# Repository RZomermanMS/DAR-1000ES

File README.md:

# Sony DAR-1000ES Conversion Project

This repository contains the project documentation converted from the original Word document into chapter-based GitHub Flavored Markdown.

## Chapters

For current AHCT wiring, brightness calculations and radio operation, start
with the [screen-driver operating guide](13-screen-driver-operating-guide.md).
Shared STB on **both** TD chips corrected the earlier multiplexing corruption;
clean 22-matrix text and scrolling were observed. Firmware 0.3.28 includes
internet radio, explicitly authorized full-width NOW PLAYING, and source
channel/bitrate/playback/genre indicators.
Installed 0.3.29 adds selectable Option 1 stereo spectrum (11 real PCM frequency
bands per channel), verified with isolated TD-model captures and decoded
stereo/mono/silence fixtures; the user confirmed the bars at 0.75% brightness.
Version 0.3.30 adds MONO 1/2 bank labels while retaining actual-source STEREO
and fixes measured scan gaps with longer DMA batching. A connected camera
snapshot confirms all 22 bars and STEREO/MONO 1/MONO 2/TUNED at 0.75%
per-grid duty. User confirmation of residual flicker is still pending;
a still image cannot establish temporal stability.
Physical voltage/current validation remains outstanding.
Firmware 0.3.31 boots with the fixed AHCT v2 GPIO map. Display output still
starts stopped; the legacy profile remains an isolated-only runtime option.
Installed firmware 0.3.32 adds eight display modes and shared short-/long-press
controls for a future Display Mode button, with 0.25% / 0.5% / 0.75% DIM cycling.
All eight modes and DIM cycling were checked on the isolated ESP; after
reconnection, Equalizer was restored at 0.75% per-grid duty.

For current display control, start with the
[fixed-element guide](08-esp-display-driver-specification.md#6-fixed-element-control-guide)
and [generic 5x7 matrix guide](08-esp-display-driver-specification.md#7-generic-5x7-matrix-guide).
The [annotated reference comparison](media/display-reference-coverage.svg)
matches every functional symbol in the FL701 drawing to an observed command.
Element mapping is complete at that level. Clean full-screen multiplexing
has now been observed with shared STB; electrical validation remains outstanding.

The [complete display bitmap catalogue](10-display-bitmap-catalogue.md)
includes 5x7 pixel patterns and HEX values for uppercase/lowercase letters,
digits, punctuation, a music note and seven level bars.

1. [DAR-1000ES Conversion](01-conversion.md)
2. [DAR-1000ES Display Control](02-display-control.md)
3. [DAR-1000ES Sound Path](03-sound-path.md)
4. [DAR-1000ES Program and Keypad Baseline](04-program-and-keypad-baseline.md)
5. [Bus Capture Findings and Key Reports](05-bus-capture-findings.md)
6. [Direct Display driving](06-direct-display-driving.md)
7. [Audio Control Findings and Next-Step Plan](07-audio-control-findings-and-plan.md)
8. [ESP32 Display-Driver Specification](08-esp-display-driver-specification.md)
9. [Music Note Bitmap](09-music-note-bitmap.md)
10. [Display Bitmap Catalogue](10-display-bitmap-catalogue.md)
11. [Live ESP32 Display Driver and Validation](11-live-display-driver-and-validation.md)
12. [TD62C950RF Timing Revalidation](12-td62c950rf-timing-revalidation.md)
13. [Screen Driver Operating Guide](13-screen-driver-operating-guide.md)
14. [Keypad Mapping](14-keypad-mapping.md)
15. [Split-setup Architecture and Travel Demo](15-split-setup-architecture.md)
16. [Internet-radio Menu Program Guide (proposed)](16-internet-radio-menu-program-guide.md)
17. [Internet-radio Menu User Instruction Manual (planned)](17-internet-radio-menu-user-manual.md)
18. [Controller ESP Implementation Specification and Agent Handoff](18-controller-esp-implementation-specification.md)

Chapters 16–17 describe a proposed directory/menu design, **not installed
firmware behavior**. For implemented controls and safety requirements, continue
to use chapters 13–15.

Images used by the chapters are stored in [`media/`](media/).

The [ESP32 firmware](firmware/README-DAR-1000ES.md) includes internet radio,
the opt-in display timing/NOW PLAYING profile and the preserved upstream license.

## Control Integration Options

1. **Reuse the original controls (partially characterized):** Investigate the parallel bus between the system controller and display/front-panel controller IC701 before bypassing the original control firmware. See the [internal bus protocol specification](SONY_DAR1000ES_Protocol_Spec.md) and [2026-11-02 capture findings](05-bus-capture-findings.md). Passive captures establish repeatable framing and key/display correlations, but masked bits, driver ownership and electrical assumptions still block reliable emulation.
2. **Direct display-driver control (optically mapped, driver experimental):** Captures at IC702/IC703 establish a 26-slot scan, 40 segment clocks and one grid clock per slot. Controlled one-hot tests now map all 770 matrix dots and all fixed functional elements shown in the reference. See the [operating guide](13-screen-driver-operating-guide.md), [element guide](08-esp-display-driver-specification.md) and [capture/validation history](06-direct-display-driving.md). Shared STB on both TD chips now gives clean full-width text and scrolling; electrical margins and current remain unverified. [DAR-1000ES Display Control](02-display-control.md) retains the original hardware proposal, not current wiring instructions.

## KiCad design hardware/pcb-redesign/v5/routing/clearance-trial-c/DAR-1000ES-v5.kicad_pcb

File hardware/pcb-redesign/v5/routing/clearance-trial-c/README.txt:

Trial C — local clearance experiment, NOT fabrication-ready
==========================================================

This is an independent derivative of placement-trial B, not an integration
with any other trial. It keeps B's placement, board outline, two antenna rule
areas, vias, pad and footprint geometry, widths, nets and all other board
data. Only endpoints of five existing B.Cu segments move at three junctions.
No new rules, exclusions, pads, layers or router were used. The long U5-VIN
segment is now slightly slanted; adjacent segments are no longer necessarily
45 degrees. Inspect manufacturability and assembly separately.

Source board SHA-256:
  2a6f2adb1d2c4078de47b7a6d337af844bace43cf1a1155d9afe8d2e7d51e7e8
Candidate board SHA-256:
  f99f7348a54bc94fd867fb7ec5e5e0f9a544eb5cf260c7a8530197dcbbef90fb
Project SHA-256:
  50232cc98a9d9072bd8f43c5f5ec578d815ad27146f54a17ccc97d2d18c3a5ed
The schematic copies are byte-identical to the original v5 hierarchy and
are retained beside the same-stem board and project for parity checks. The
footprint table points back to the original v5 library.

Observed changes, native KiCad copper-shape distances
---------------------------------------------------
Measurements compare the retained placement-trial/trial-b-tht-clearance.json
with tht-clearance.json, using the same KiCad 10.0.2 tool and 0.50 mm cutoff.
Unrelated plated-through-hole pad vs track/via pairs are counted per common
copper layer and segment, not unique locations.

* U11 pad 3 to the horizontal SONY_5V_SENSE segment, B.Cu:
  0.201700 -> 0.351701 mm; this is also that pad's measured local minimum.
* U1-CONTROLLER1 J3.11–J3.22 to the long U5-VIN segment, B.Cu: each
  0.201700 -> 0.398570 down to 0.224405 mm, respectively.
  At J3.11 the adjacent diagonal improves 0.201657 -> 0.261535 mm;
  that diagonal remains the pad's nearest unrelated track.
* Across the entire board, pairs below 0.30 mm decrease from 330 to 322;
  the 0.50 mm report has 465 pairs both before and after. Among pairs present
  in both reports 14 distances increase and none decrease; no pairs enter or
  leave that cutoff. This comparison does not imply anything about pairs
  outside the cutoff, pad-to-pad, zones, non-PTH holes or non-PTH pads.
* The board-wide minimum remains 0.201657 mm at another pad/track pair.
  Thus this does NOT establish generous or universal 0.30 mm spacing.

The initial test moved the entire U5-VIN segment 0.20 mm left and the IO4
segment by R3 0.15 mm upward, along with the U11 move. It failed native DRC:
four track-to-track conflicts at IO4/IO42 and a 0.1828 mm track-to-C8 pad
gap. Those shifts were not retained. The final change moves only the upper
U5-VIN junction, preserving its remote diagonal and avoiding that conflict.
No claim is made that this small, local search is optimal or exhaustive.

Validation and limitations
--------------------------
drc.json and drc-parity.json: native KiCad 10.0.2, zero violations, zero
unconnected items; the latter also reports zero schematic parity issues.
The project has no DRC exclusions and missing-courtyard is an error. Four
checks remain ignored: track_not_centered_on_via, tuning_profile_track_
geometries, footprint_filters_mismatch, footprint_type_mismatch. A zero
report does not verify them. audit.txt records the retained netlist/319 node,
exact UART endpoints, y=150 mm section and component-envelope audits.
It also verifies the exact board text differs only in the five intended
segment endpoint coordinates; there are 715 segments, seven vias and 0.30 mm
minimum track width. The retained measurement and board-audit unit suites
passed (7 and 10 tests). These audits do not model plugs, cables, installed
modules, chassis, RF, electrical return paths or the actual antenna keepout.
Trial B's decoupling limitations still apply; no circuit, mechanical, thermal,
RF, safety, fabrication or assembly approval is implied.

Reproduction (repository root)
------------------------------
Requires Docker image kicad/kicad:10.0.2 (observed digest
sha256:165c81785b2df23a09892f4cc53bc0095a83b469bfbbe07989670d64049677a7).
Use an existing writable OUT directory outside the repository. No router JAR
is needed. The container runs with the repository read-only; HOME is
deliberately unwritable, so KiCad may print configuration-directory errors.

  P=hardware/pcb-redesign/v5/routing/clearance-trial-c
  V=hardware/pcb-redesign/v5
  docker run --rm --network none --user "$(id -u):$(id -g)" \
    -e HOME=/nonexistent -e PYTHONDONTWRITEBYTECODE=1 \
    -v "$PWD:/work:ro" -v "$OUT:/out:rw" --entrypoint /usr/bin/python3 \
    kicad/kicad:10.0.2 /work/$P/build.py \
    /work/$V/routing/placement-trial/silk-b/result.kicad_pcb /out/rebuilt.kicad_pcb
  sha256sum "$OUT/rebuilt.kicad_pcb" "$P/DAR-1000ES-v5.kicad_pcb"
  docker run --rm --network none --user "$(id -u):$(id -g)" \
    -e HOME=/nonexistent -e PYTHONDONTWRITEBYTECODE=1 -v "$PWD:/work:ro" \
    -v "$OUT:/out:ro" --entrypoint /usr/bin/python3 kicad/kicad:10.0.2 \
    /work/$P/audit.py /work/$V/routing/placement-trial/silk-b/result.kicad_pcb \
    /out/rebuilt.kicad_pcb /work/$V/DAR-1000ES-v5.net.xml
  docker run --rm --network none --user "$(id -u):$(id -g)" \
    -e HOME=/nonexistent -v "$PWD:/work:ro" --entrypoint kicad-cli \
    kicad/kicad:10.0.2 pcb drc --schematic-parity --format json -o /dev/stdout \
    /work/$P/DAR-1000ES-v5.kicad_pcb
  docker run --rm --network none --user "$(id -u):$(id -g)" \
    -e HOME=/nonexistent -e PYTHONDONTWRITEBYTECODE=1 -v "$PWD:/work:ro" \
    --entrypoint /usr/bin/python3 kicad/kicad:10.0.2 \
    /work/$V/routing/measure_tht_clearance.py /work/$P/DAR-1000ES-v5.kicad_pcb

The parity command checks the retained candidate; first compare the rebuilt
hash to establish it is the same board. Separate normal DRC omits
--schematic-parity. Report dates and tool logs need not be bit-identical.

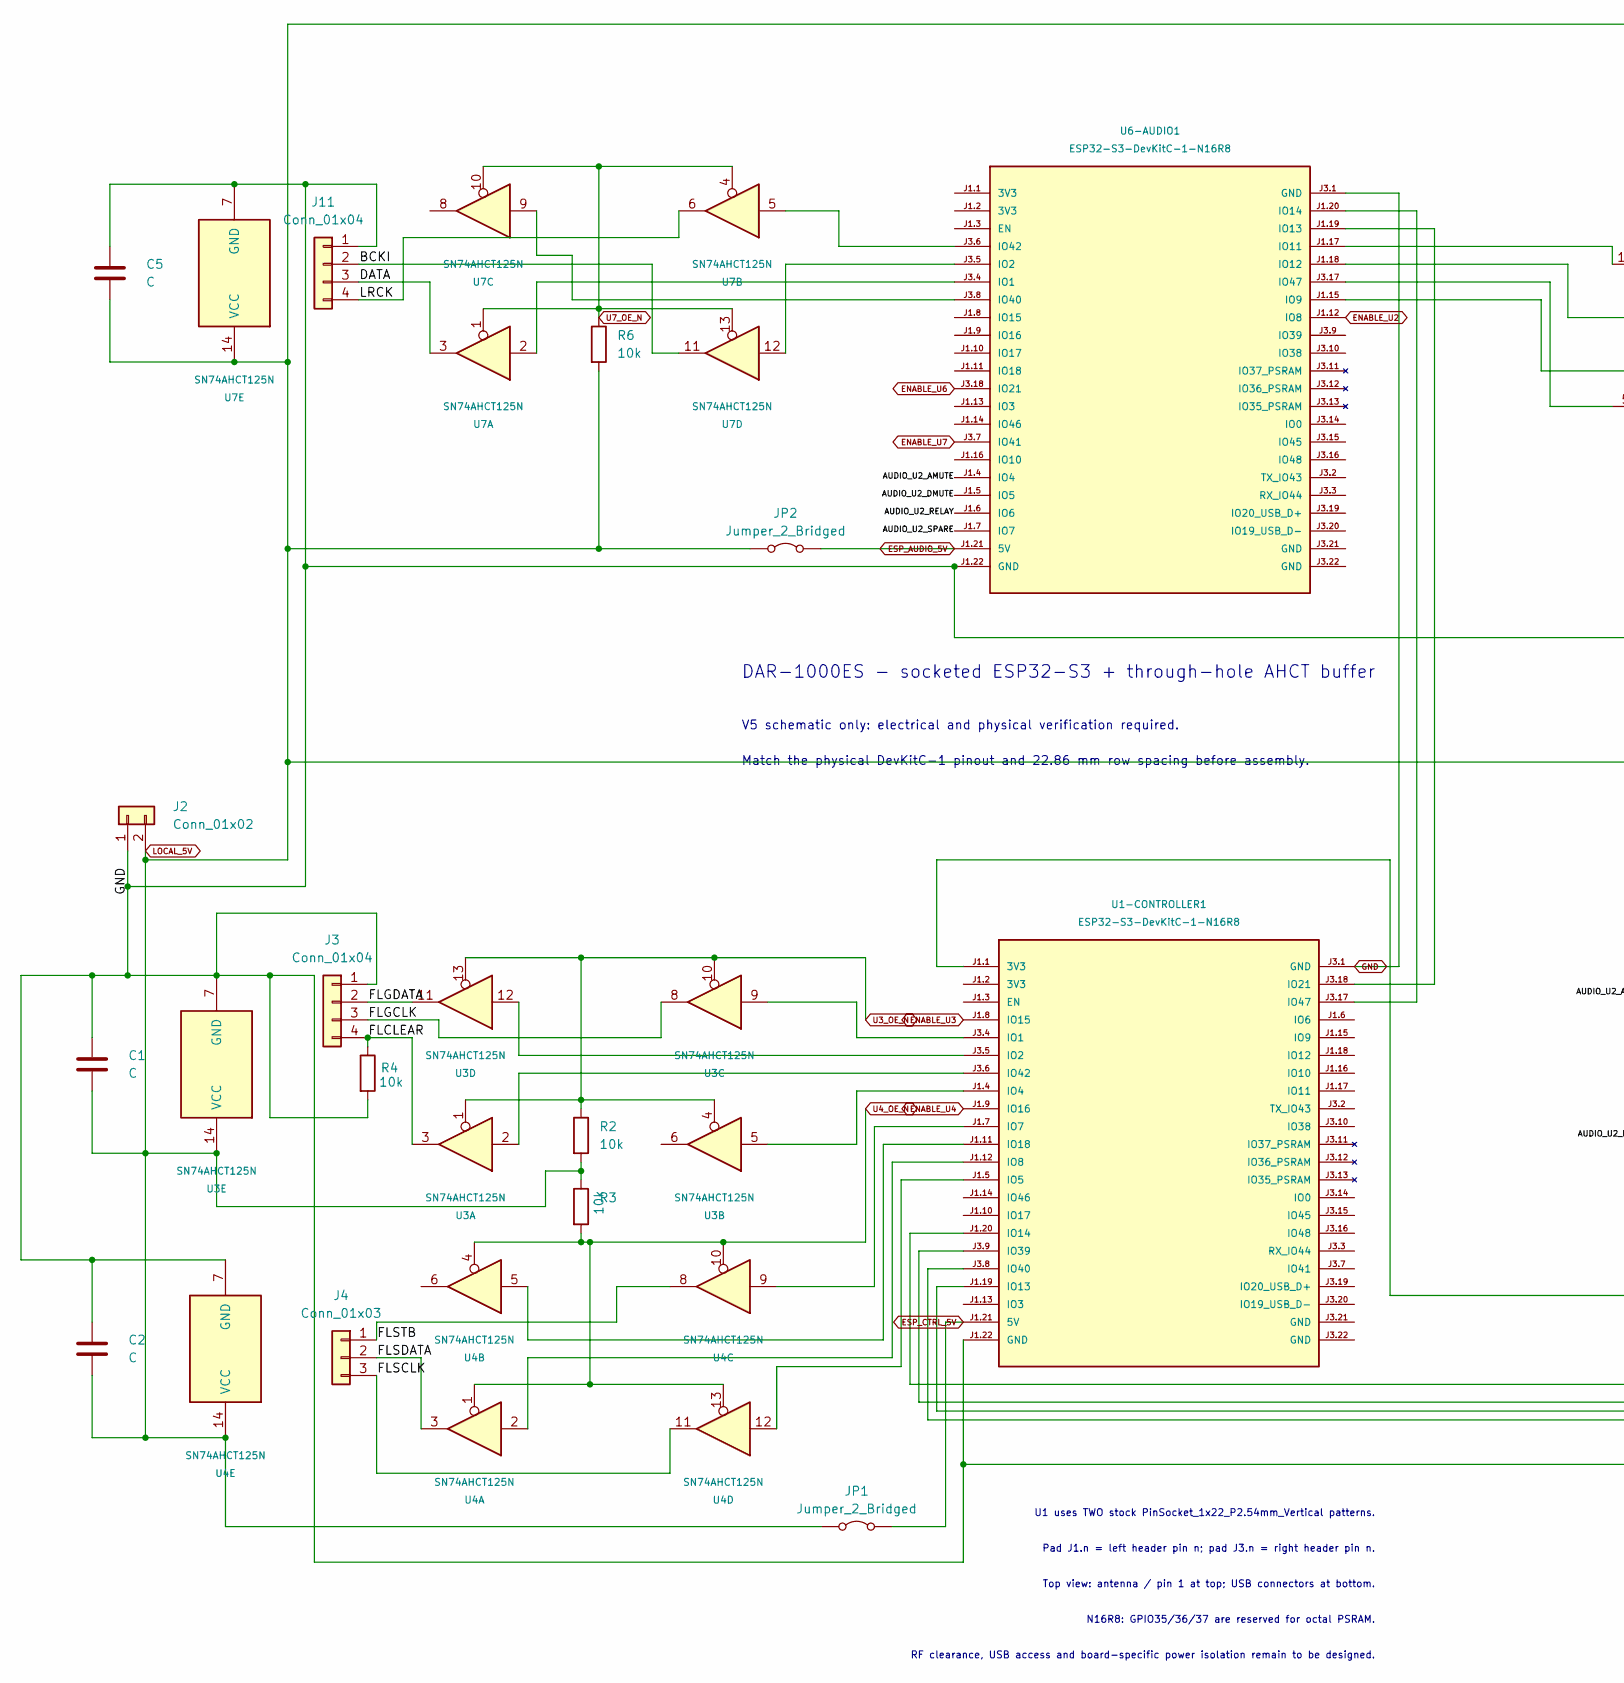
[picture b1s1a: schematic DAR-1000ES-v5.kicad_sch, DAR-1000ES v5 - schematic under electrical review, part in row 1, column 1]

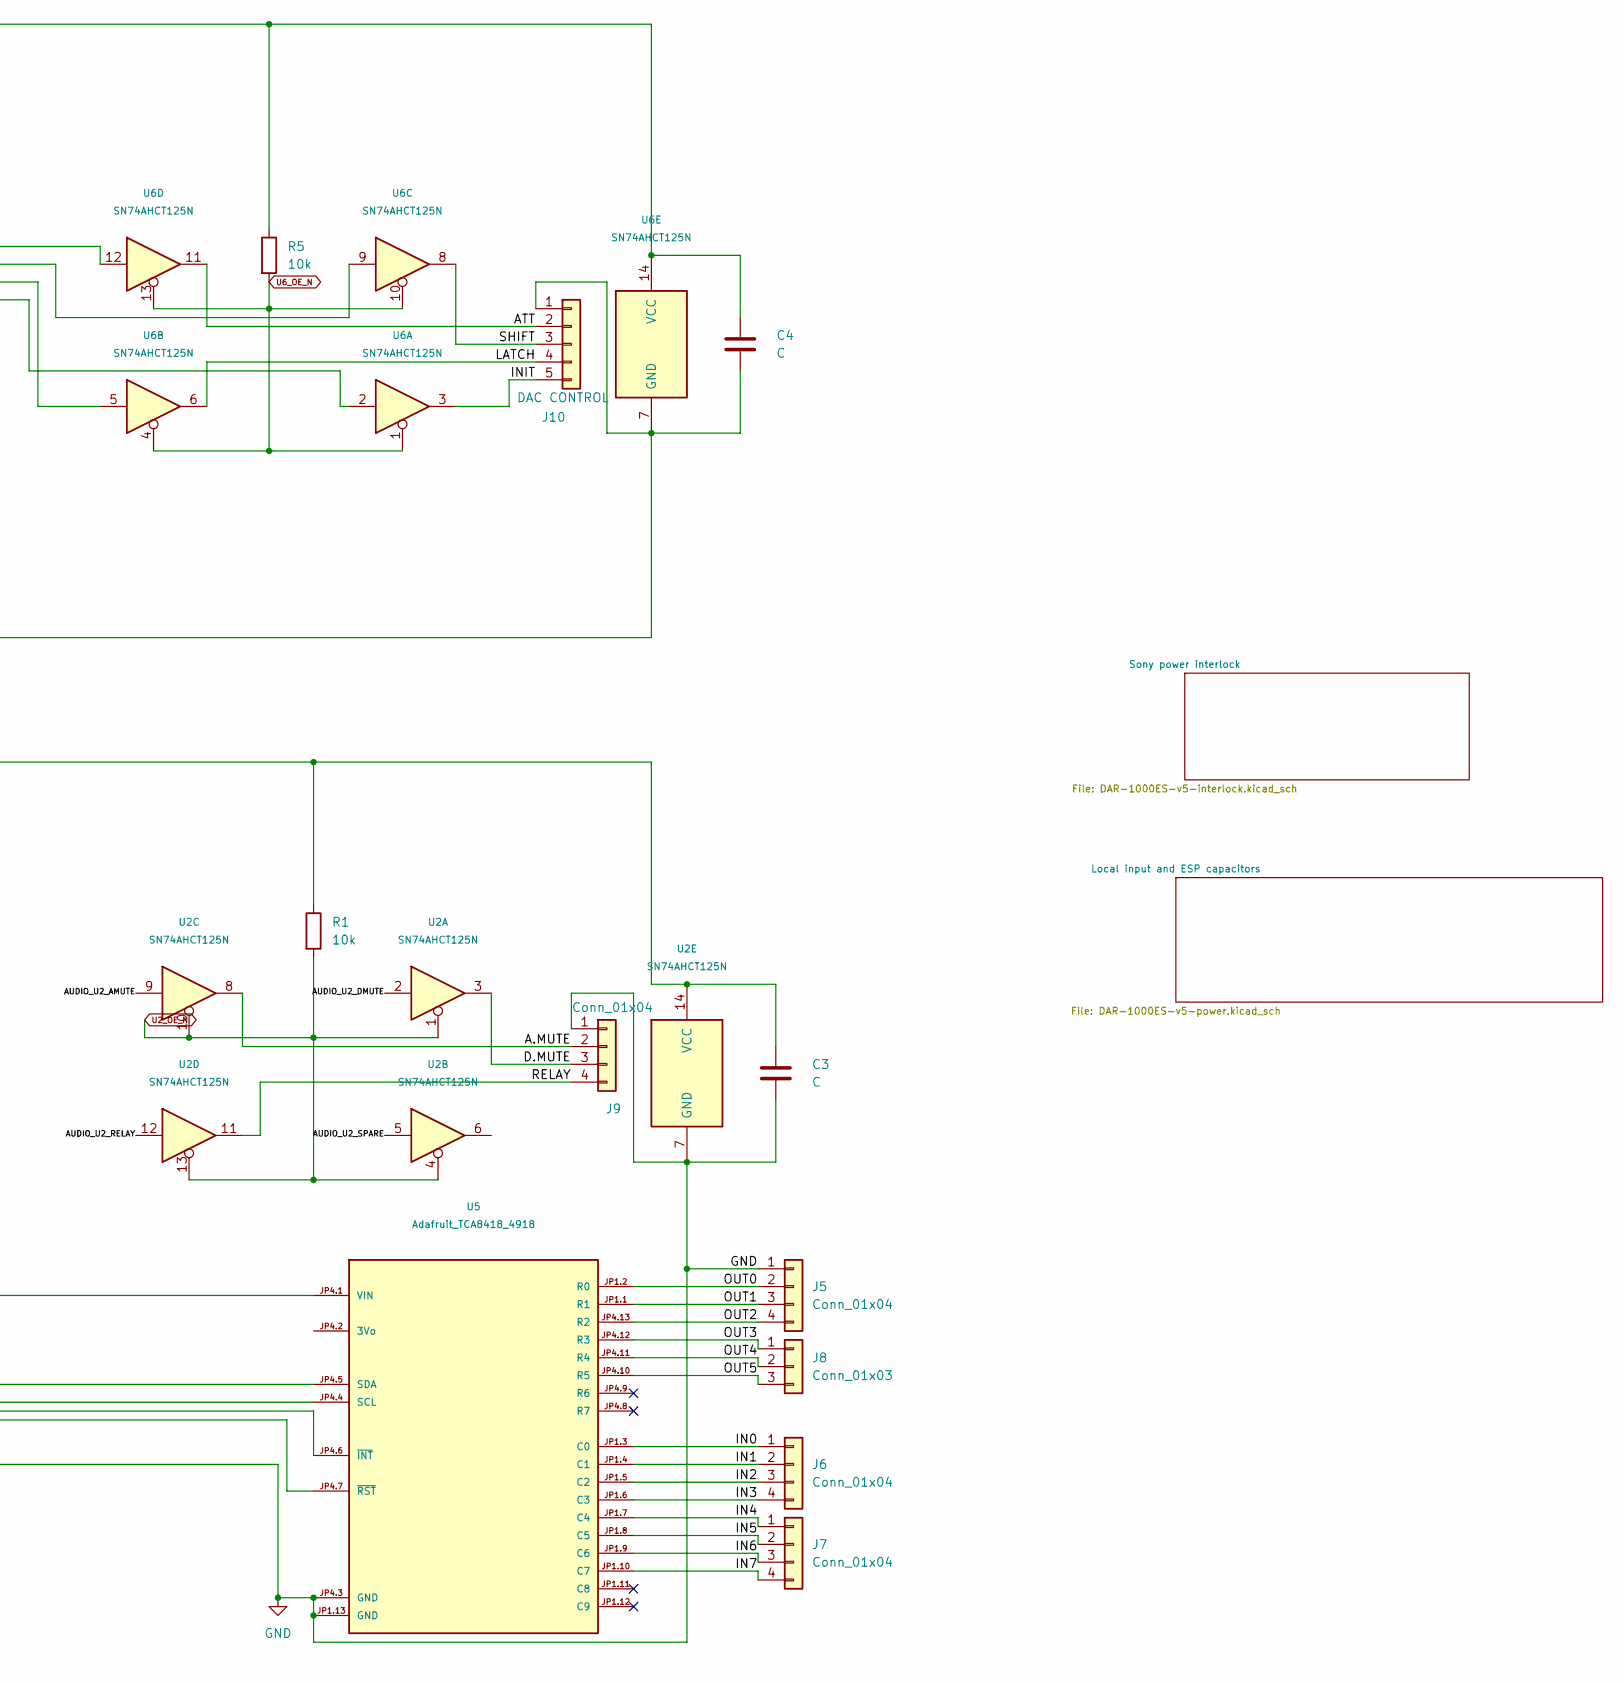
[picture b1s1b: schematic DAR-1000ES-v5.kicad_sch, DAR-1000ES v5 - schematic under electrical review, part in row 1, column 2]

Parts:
C1, C2, C3, C4, C5: C; Bottom_Capacitor_THT__C_Disc_D5.0mm_W2.5mm_P5.00mm
J2: Conn_01x02; Bottom_Connector_JST__JST_XH_S2B-XH-A_1x02_P2.50mm_Horizont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
J3, J5, J6, J7, J9, J11: Conn_01x04; Bottom_Connector_JST__JST_XH_S4B-XH-A_1x04_P2.50mm_Horizont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
J4, J8: Conn_01x03; Bottom_Connector_JST__JST_XH_S3B-XH-A_1x03_P2.50mm_Horizont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
J10: DAC CONTROL; Bottom_Connector_JST__JST_XH_S5B-XH-A_1x05_P2.50mm_Horizont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
JP1, JP2: Jumper_2_Bridged; Bottom_Connector_PinHeader_2.54mm__PinHeader_1x02_P2.54mm_V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
R1, R2, R3, R4, R5, R6: 10k; Bottom_Resistor_THT__R_Axial_DIN0207_L6.3mm_D2.5mm_P7.62mm_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
U1-CONTROLLER1, U6-AUDIO1: ESP32-S3-DevKitC-1-N16R8; Bottom_DAR1000ES__ESP32-S3-DevKitC-1_2xSocket_1x22_P2.54mm_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; MPN ESP32-S3-DevKitC-1-N16R8
U2, U3, U4, U6, U7: SN74AHCT125N; Bottom_Package_DIP__DIP-14_W7.62mm; MPN SN74AHCT125N
U5: Adafruit_TCA8418_4918; Bottom_DAR1000ES__Adafruit_TCA8418_4918_2x13_P2.54mm_W12.70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; MPN 4918

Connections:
/A.MUTE: J9.2, U2.8
/ATT: J10.2, U6.11
/AUDIO_U2_AMUTE: U2.9, U6-AUDIO1.J1.4 (IO4)
/AUDIO_U2_DMUTE: U2.2, U6-AUDIO1.J1.5 (IO5)
/AUDIO_U2_RELAY: U2.12, U6-AUDIO1.J1.6 (IO6)
/AUDIO_U2_SPARE: U2.5, U6-AUDIO1.J1.7 (IO7)
/BCKI: J11.2, U7.11
/D.MUTE: J9.3, U2.3
/DATA: J11.3, U7.3
/FLCLEAR: J3.4, R4.1, U3.3
/FLGCLK: J3.3, U3.8
/FLGDATA: J3.2, U3.11
/FLSCLK: J4.3, U4.11
/FLSDATA: J4.2, U4.3
/FLSTB: J4.1, U4.8
/IN0: J6.1, U5.JP1.3 (C0)
/IN1: J6.2, U5.JP1.4 (C1)
/IN2: J6.3, U5.JP1.5 (C2)
/IN3: J6.4, U5.JP1.6 (C3)
/IN4: J7.1, U5.JP1.7 (C4)
/IN5: J7.2, U5.JP1.8 (C5)
/IN6: J7.3, U5.JP1.9 (C6)
/IN7: J7.4, U5.JP1.10 (C7)
/INIT: J10.5, U6.3
/LATCH: J10.4, U6.6
/LRCK: J11.4, U7.6
/OUT0: J5.2, U5.JP1.2 (R0)
/OUT1: J5.3, U5.JP1.1 (R1)
/OUT2: J5.4, U5.JP4.13 (R2)
/OUT3: J8.1, U5.JP4.12 (R3)
/OUT4: J8.2, U5.JP4.11 (R4)
/OUT5: J8.3, U5.JP4.10 (R5)
/RELAY: J9.4, U2.11
/SHIFT: J10.3, U6.8
ENABLE_U2: U6-AUDIO1.J1.12 (IO8); also elsewhere on the board
ENABLE_U3: U1-CONTROLLER1.J1.8 (IO15); also elsewhere on the board
ENABLE_U4: U1-CONTROLLER1.J1.9 (IO16); also elsewhere on the board
ENABLE_U6: U6-AUDIO1.J3.18 (IO21); also elsewhere on the board
ENABLE_U7: U6-AUDIO1.J3.7 (IO41); also elsewhere on the board
ESP_AUDIO_5V: JP2.2 (B), U6-AUDIO1.J1.21 (5V); also elsewhere on the board
ESP_CTRL_5V: JP1.2 (B), U1-CONTROLLER1.J1.21 (5V); also elsewhere on the board
GND: C1.1, C2.1, C3.2, C4.2, C5.1, J2.1, J3.1, J5.1, J9.1, J10.1, J11.1, R4.2, U1-CONTROLLER1.J1.22 (GND), U1-CONTROLLER1.J3.1 (GND), U2.7 (GND), U3.7 (GND), U4.7 (GND), U5.JP1.13 (GND), U5.JP4.3 (GND), U6.7 (GND), U6-AUDIO1.J1.22 (GND), U6-AUDIO1.J3.1 (GND), U7.7 (GND); also elsewhere on the board
LOCAL_5V: C1.2, C2.2, C3.1, C4.1, C5.2, J2.2, JP1.1 (A), JP2.1 (A), R1.1, R2.2, R3.1, R5.1, R6.2, U2.14 (VCC), U3.14 (VCC), U4.14 (VCC), U6.14 (VCC), U7.14 (VCC); also elsewhere on the board
unnamed: U1-CONTROLLER1.J3.4 (IO1), U3.9
unnamed: U1-CONTROLLER1.J3.5 (IO2), U3.12
unnamed: U1-CONTROLLER1.J1.4 (IO4), U3.5
unnamed: U1-CONTROLLER1.J1.5 (IO5), U4.12
unnamed: U1-CONTROLLER1.J1.7 (IO7), U4.9
unnamed: U1-CONTROLLER1.J1.12 (IO8), U4.2
unnamed: U1-CONTROLLER1.J1.19 (IO13), U5.JP4.6 (~INT)
unnamed: U1-CONTROLLER1.J1.20 (IO14), U5.JP4.5 (SDA)
unnamed: U1-CONTROLLER1.J1.11 (IO18), U4.5
unnamed: U1-CONTROLLER1.J3.18 (IO21), U6-AUDIO1.J1.19 (IO13)
unnamed: U1-CONTROLLER1.J3.9 (IO39), U5.JP4.4 (SCL)
unnamed: U1-CONTROLLER1.J3.8 (IO40), U5.JP4.7 (~RST)
unnamed: U1-CONTROLLER1.J3.6 (IO42), U3.2
unnamed: U1-CONTROLLER1.J3.17 (IO47), U6-AUDIO1.J1.20 (IO14)
unnamed: U1-CONTROLLER1.J1.1 (3V3), U5.JP4.1 (VIN)
unnamed: U6-AUDIO1.J3.4 (IO1), U7.2
unnamed: U6-AUDIO1.J3.5 (IO2), U7.12
unnamed: U6.2, U6-AUDIO1.J1.15 (IO9)
unnamed: U6.12, U6-AUDIO1.J1.17 (IO11)
unnamed: U6.9, U6-AUDIO1.J1.18 (IO12)
unnamed: U6-AUDIO1.J3.8 (IO40), U7.9
unnamed: U6-AUDIO1.J3.6 (IO42), U7.5
unnamed: U6.5, U6-AUDIO1.J3.17 (IO47)
U2_OE_N: R1.2, U2.1, U2.4, U2.10, U2.13; also elsewhere on the board
U3_OE_N: R2.1, U3.1, U3.4, U3.10, U3.13; also elsewhere on the board
U4_OE_N: R3.2, U4.1, U4.4, U4.10, U4.13; also elsewhere on the board
U6_OE_N: R5.2, U6.1, U6.4, U6.10, U6.13; also elsewhere on the board
U7_OE_N: R6.1, U7.1, U7.4, U7.10, U7.13; also elsewhere on the board

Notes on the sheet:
RF clearance, USB access and board-specific power isolation remain to be designed.
Pad J1.n = left header pin n; pad J3.n = right header pin n.
DAR-1000ES - socketed ESP32-S3 + through-hole AHCT buffer
U1 uses TWO stock PinSocket_1x22_P2.54mm_Vertical patterns.
Top view: antenna / pin 1 at top; USB connectors at bottom.
N16R8: GPIO35/36/37 are reserved for octal PSRAM.
Match the physical DevKitC-1 pinout and 22.86 mm row spacing before assembly.
V5 schematic only: electrical and physical verification required.

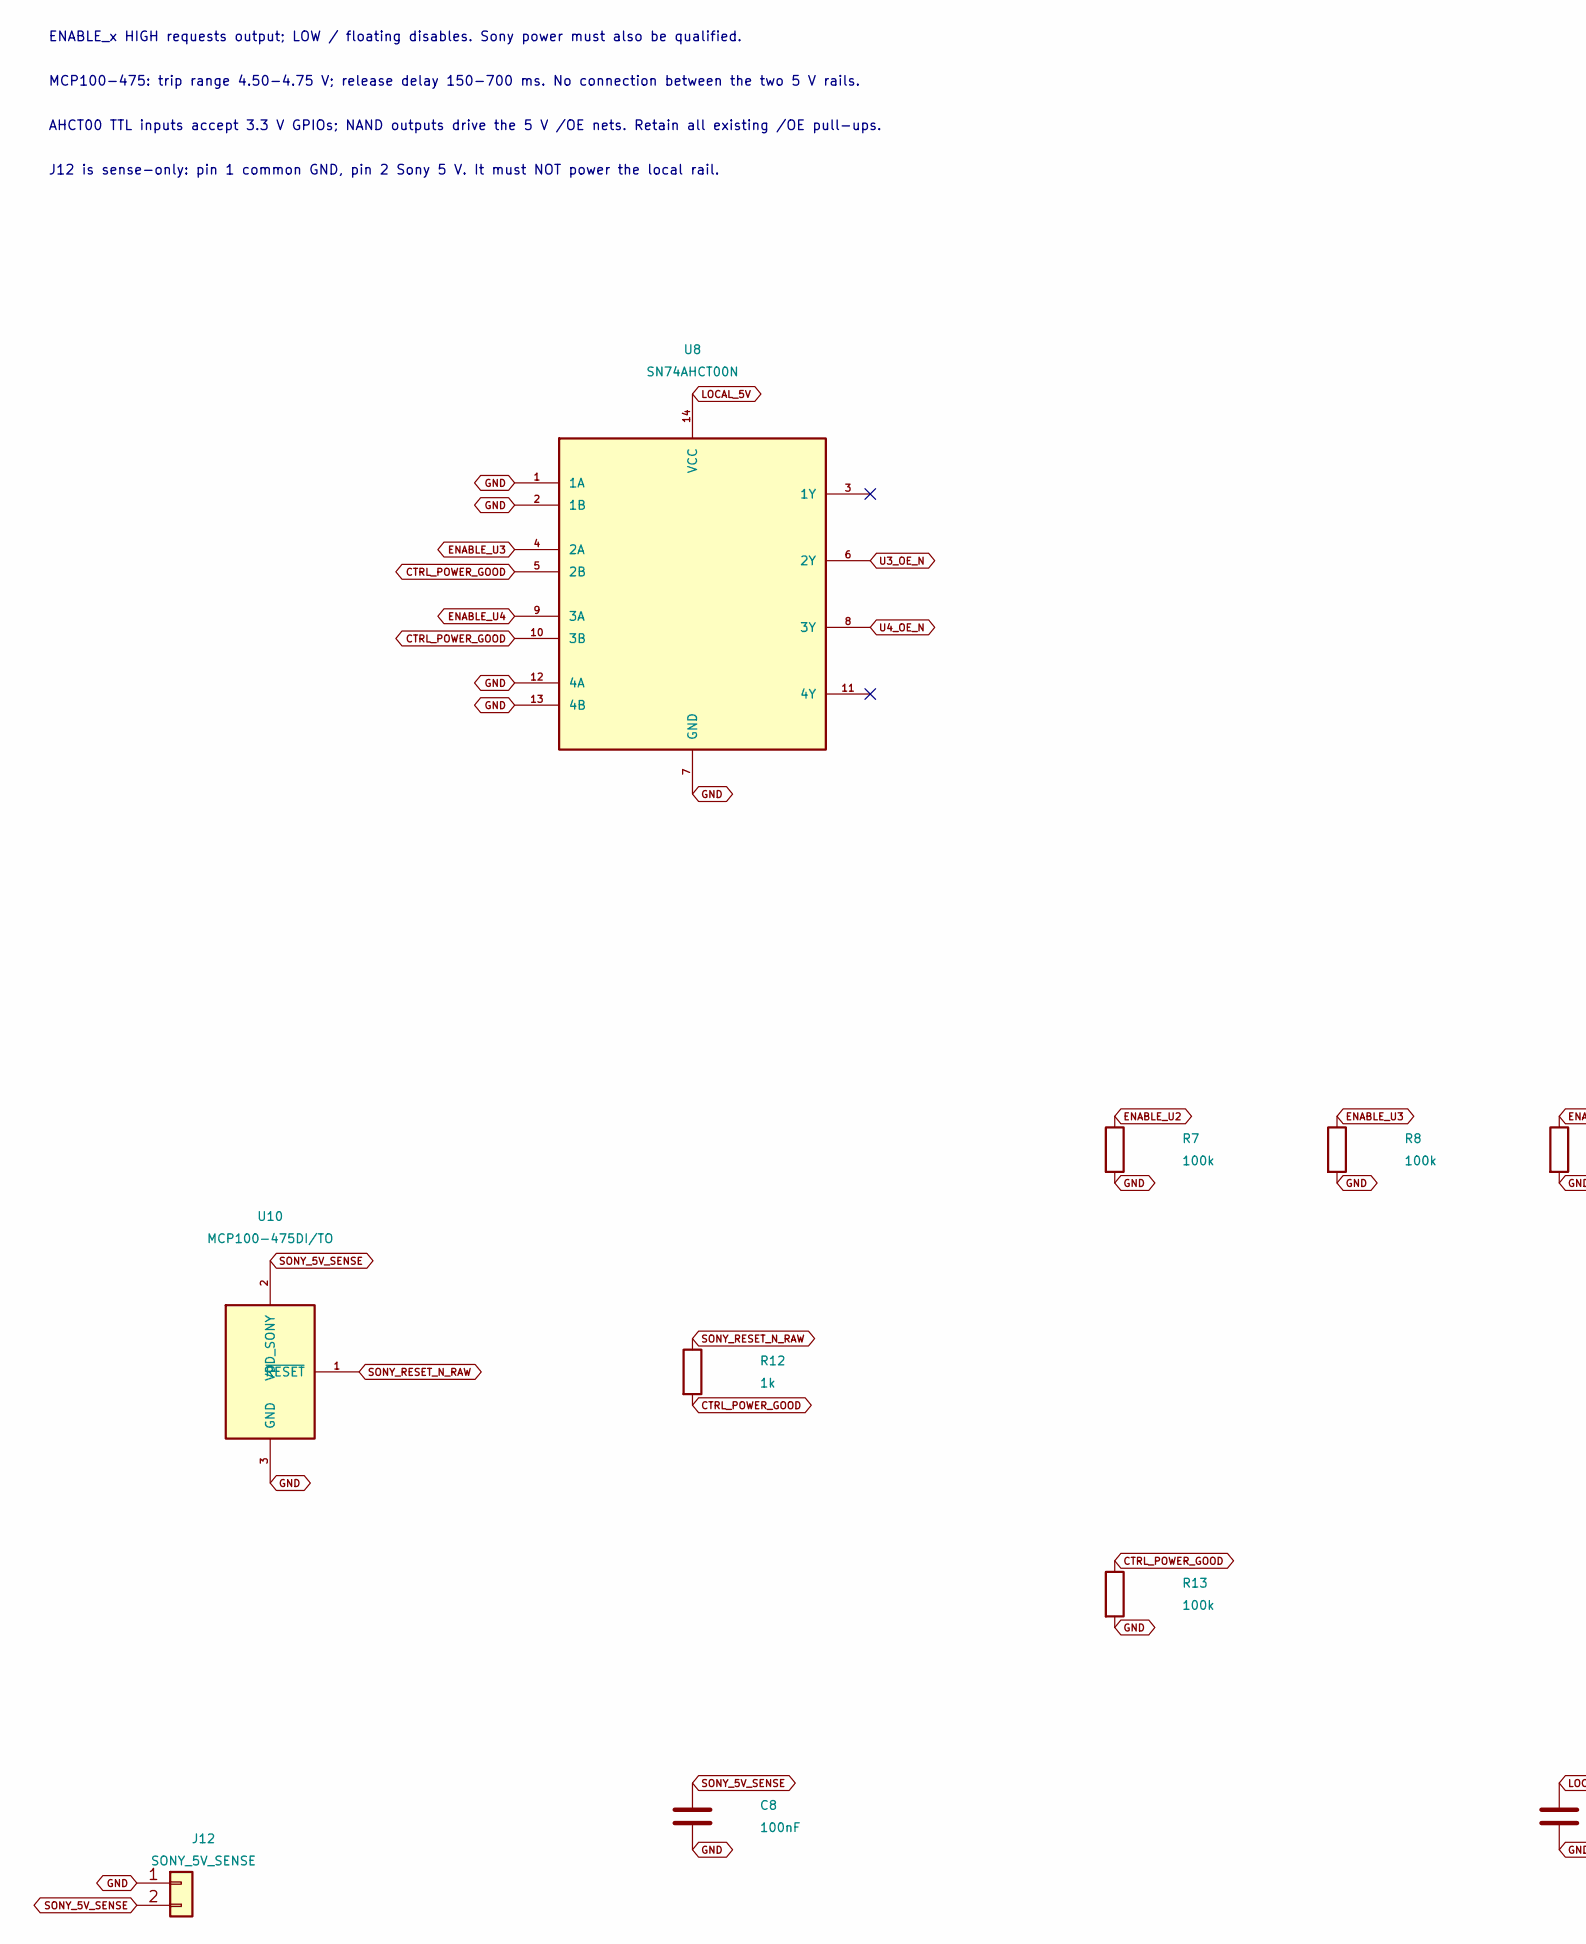
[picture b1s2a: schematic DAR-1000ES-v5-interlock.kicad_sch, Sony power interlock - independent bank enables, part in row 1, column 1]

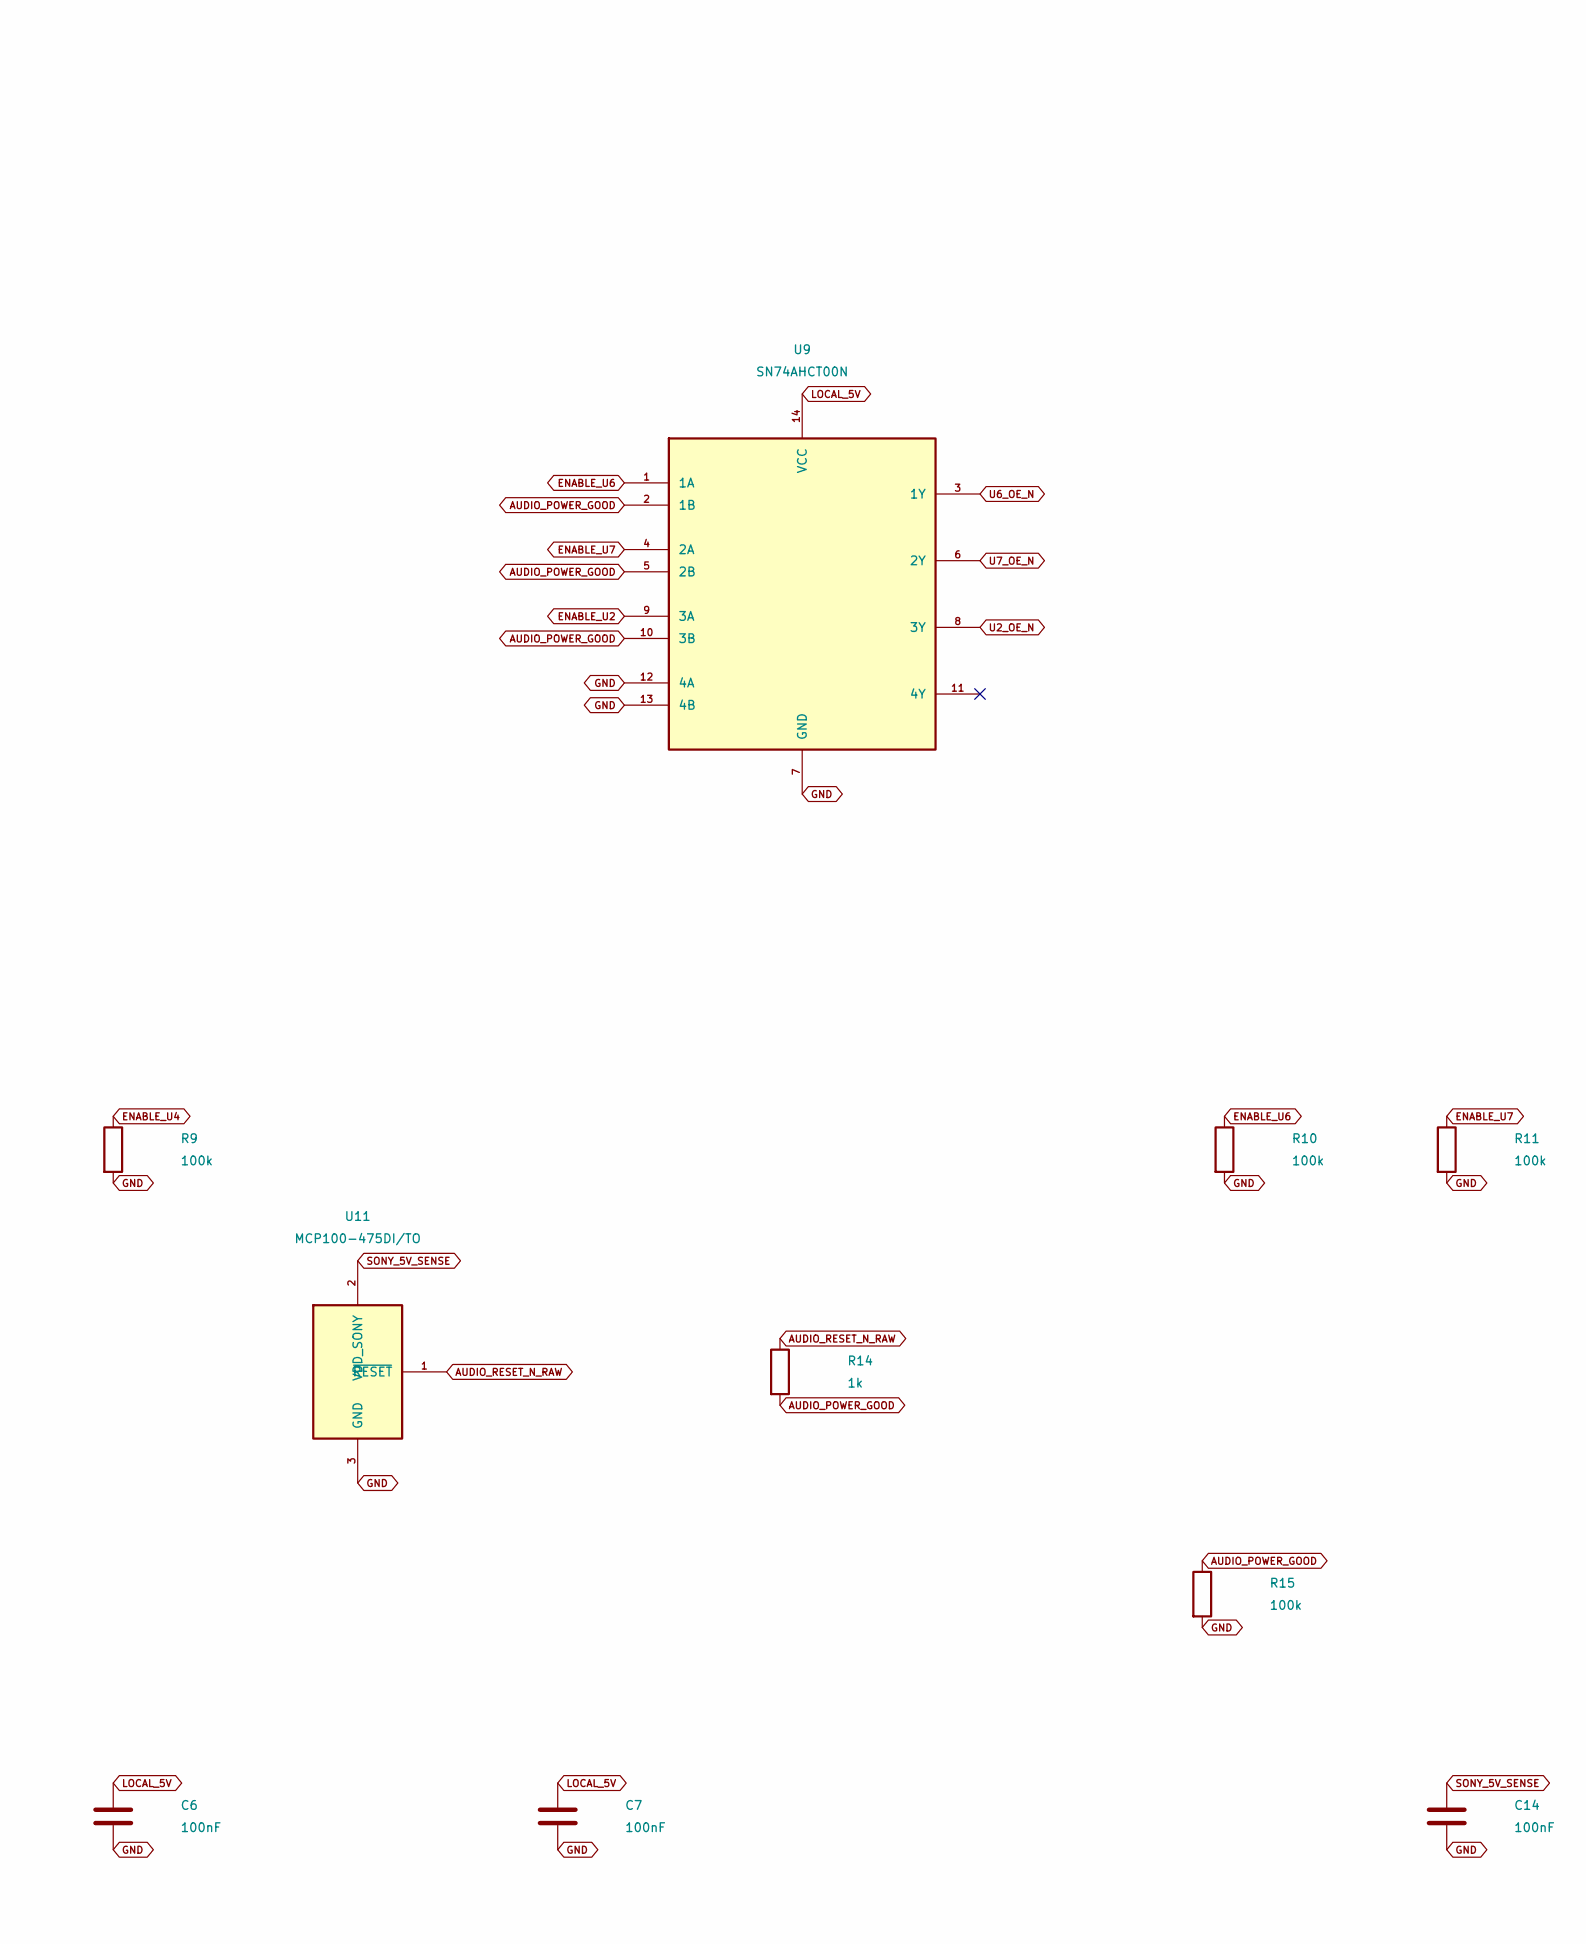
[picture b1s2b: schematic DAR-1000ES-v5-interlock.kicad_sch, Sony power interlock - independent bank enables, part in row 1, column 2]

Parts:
C6, C7, C8, C14: 100nF; Bottom_Capacitor_THT__C_Disc_D5.0mm_W2.5mm_P5.00mm
J12: SONY_5V_SENSE; Bottom_Connector_JST__JST_XH_S2B-XH-A_1x02_P2.50mm_Horizont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
R7, R8, R9, R10, R11, R13, R15: 100k; Bottom_Resistor_THT__R_Axial_DIN0207_L6.3mm_D2.5mm_P7.62mm_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
R12, R14: 1k; Bottom_Resistor_THT__R_Axial_DIN0207_L6.3mm_D2.5mm_P7.62mm_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
U8, U9: SN74AHCT00N; Bottom_Package_DIP__DIP-14_W7.62mm
U10, U11: MCP100-475DI/TO; Bottom_Package_TO_SOT_THT__TO-92_Inline

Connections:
AUDIO_POWER_GOOD: R14.2, R15.1, U9.2 (1B), U9.5 (2B), U9.10 (3B)
AUDIO_RESET_N_RAW: R14.1, U11.1 (~RESET)
CTRL_POWER_GOOD: R12.2, R13.1, U8.5 (2B), U8.10 (3B)
ENABLE_U2: R7.1, U9.9 (3A); also elsewhere on the board
ENABLE_U3: R8.1, U8.4 (2A); also elsewhere on the board
ENABLE_U4: R9.1, U8.9 (3A); also elsewhere on the board
ENABLE_U6: R10.1, U9.1 (1A); also elsewhere on the board
ENABLE_U7: R11.1, U9.4 (2A); also elsewhere on the board
GND: C6.2, C7.2, C8.2, C14.2, J12.1, R7.2, R8.2, R9.2, R10.2, R11.2, R13.2, R15.2, U8.1 (1A), U8.2 (1B), U8.7 (GND), U8.12 (4A), U8.13 (4B), U9.7 (GND), U9.12 (4A), U9.13 (4B), U10.3 (GND), U11.3 (GND); also elsewhere on the board
LOCAL_5V: C6.1, C7.1, U8.14 (VCC), U9.14 (VCC); also elsewhere on the board
SONY_5V_SENSE: C8.1, C14.1, J12.2, U10.2 (VDD_SONY), U11.2 (VDD_SONY)
SONY_RESET_N_RAW: R12.1, U10.1 (~RESET)
U2_OE_N: U9.8 (3Y); also elsewhere on the board
U3_OE_N: U8.6 (2Y); also elsewhere on the board
U4_OE_N: U8.8 (3Y); also elsewhere on the board
U6_OE_N: U9.3 (1Y); also elsewhere on the board
U7_OE_N: U9.6 (2Y); also elsewhere on the board

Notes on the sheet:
ENABLE_x HIGH requests output; LOW / floating disables. Sony power must also be qualified.
MCP100-475: trip range 4.50-4.75 V; release delay 150-700 ms. No connection between the two 5 V rails.
AHCT00 TTL inputs accept 3.3 V GPIOs; NAND outputs drive the 5 V /OE nets. Retain all existing /OE pull-ups.
J12 is sense-only: pin 1 common GND, pin 2 Sony 5 V. It must NOT power the local rail.

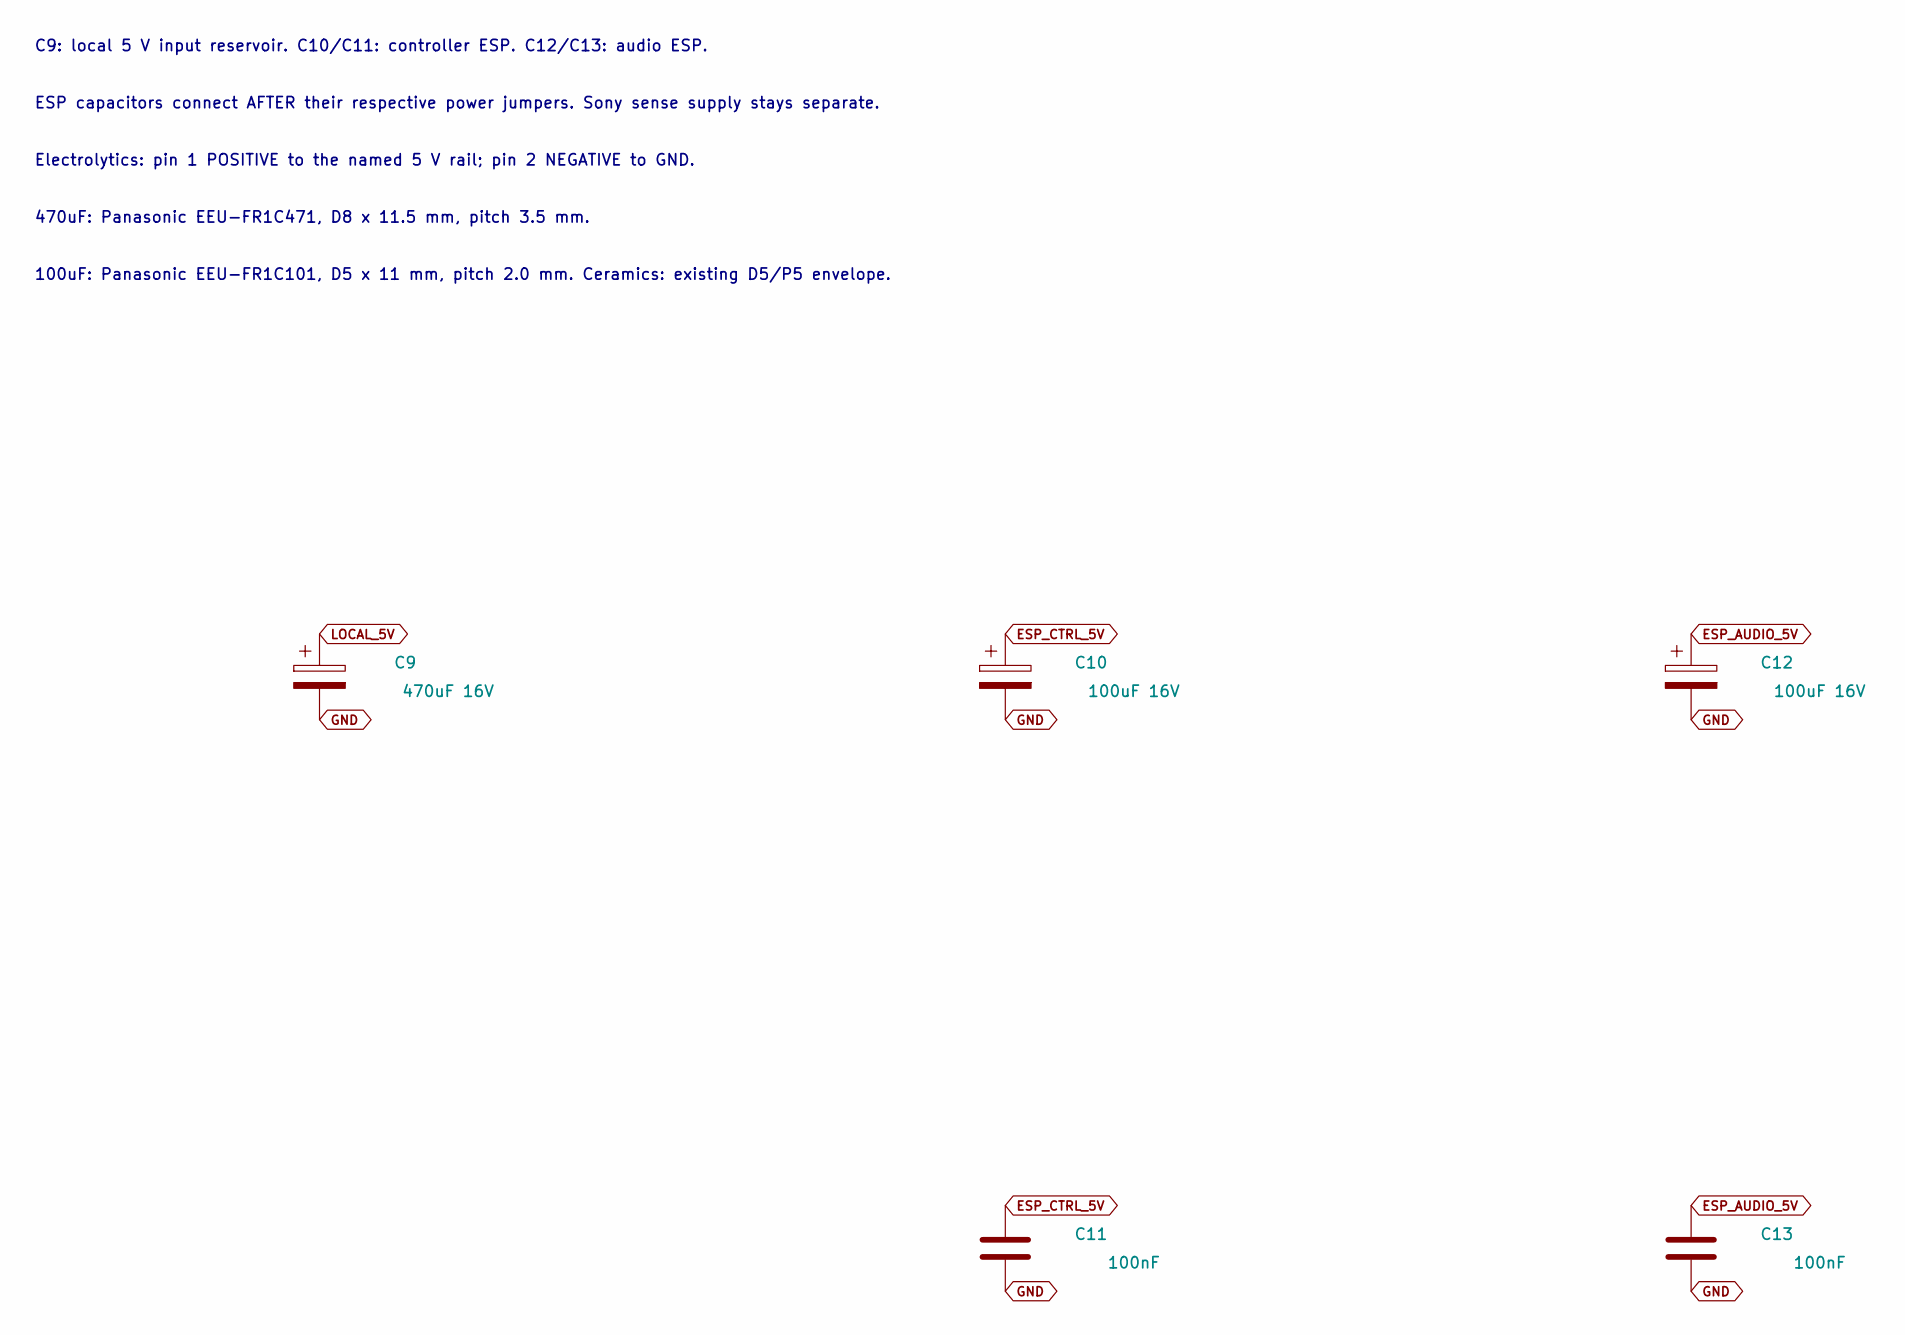
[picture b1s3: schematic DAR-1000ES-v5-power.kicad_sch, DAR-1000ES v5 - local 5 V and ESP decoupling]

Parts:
C9: 470uF 16V; Bottom_Capacitor_THT__CP_Radial_D8.0mm_P3.50mm; MPN EEU-FR1C471
C10, C12: 100uF 16V; Bottom_Capacitor_THT__CP_Radial_D5.0mm_P2.00mm; MPN EEU-FR1C101
C11, C13: 100nF; Bottom_Capacitor_THT__C_Disc_D5.0mm_W2.5mm_P5.00mm

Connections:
ESP_AUDIO_5V: C12.1, C13.1; also elsewhere on the board
ESP_CTRL_5V: C10.1, C11.1; also elsewhere on the board
GND: C9.2, C10.2, C11.2, C12.2, C13.2; also elsewhere on the board
LOCAL_5V: C9.1; also elsewhere on the board

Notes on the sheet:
C9: local 5 V input reservoir. C10/C11: controller ESP. C12/C13: audio ESP.
ESP capacitors connect AFTER their respective power jumpers. Sony sense supply stays separate.
Electrolytics: pin 1 POSITIVE to the named 5 V rail; pin 2 NEGATIVE to GND.
470uF: Panasonic EEU-FR1C471, D8 x 11.5 mm, pitch 3.5 mm.
100uF: Panasonic EEU-FR1C101, D5 x 11 mm, pitch 2.0 mm. Ceramics: existing D5/P5 envelope.

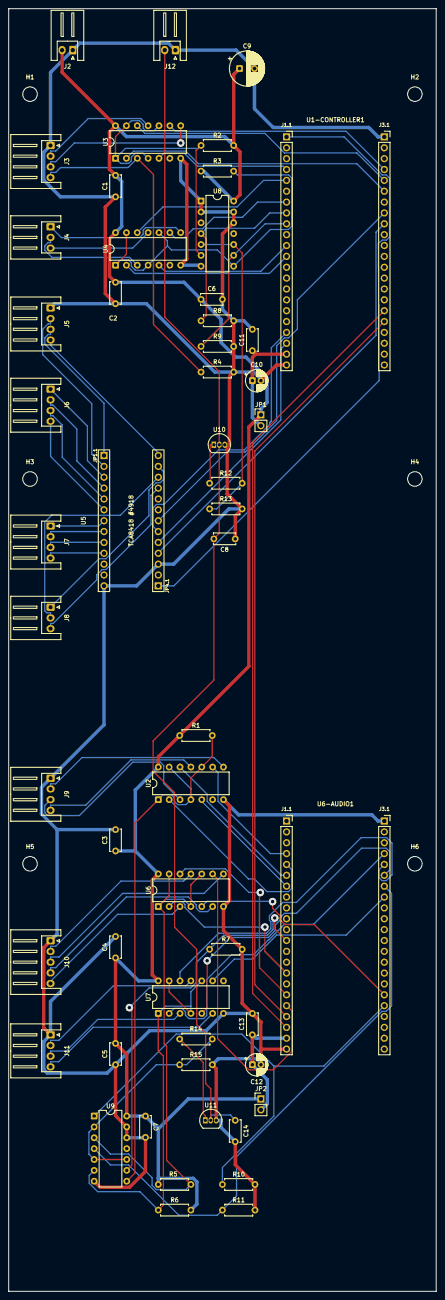
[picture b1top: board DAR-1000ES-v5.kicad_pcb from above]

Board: 2 copper layers, 100.0 x 300.0 mm, 60 parts (0 on the bottom side), 76 nets.

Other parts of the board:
H1, H2, H3, H4, H5, H6: M3_Clearance_3.4mm; MountingHole_3.4mm_M3_NPTH

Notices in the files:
parts and their libraries:
License: CC-BY-SA-3.0
